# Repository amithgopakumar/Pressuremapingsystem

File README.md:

# ESP32 PCB designed for using FSR sensor to measure the pressure

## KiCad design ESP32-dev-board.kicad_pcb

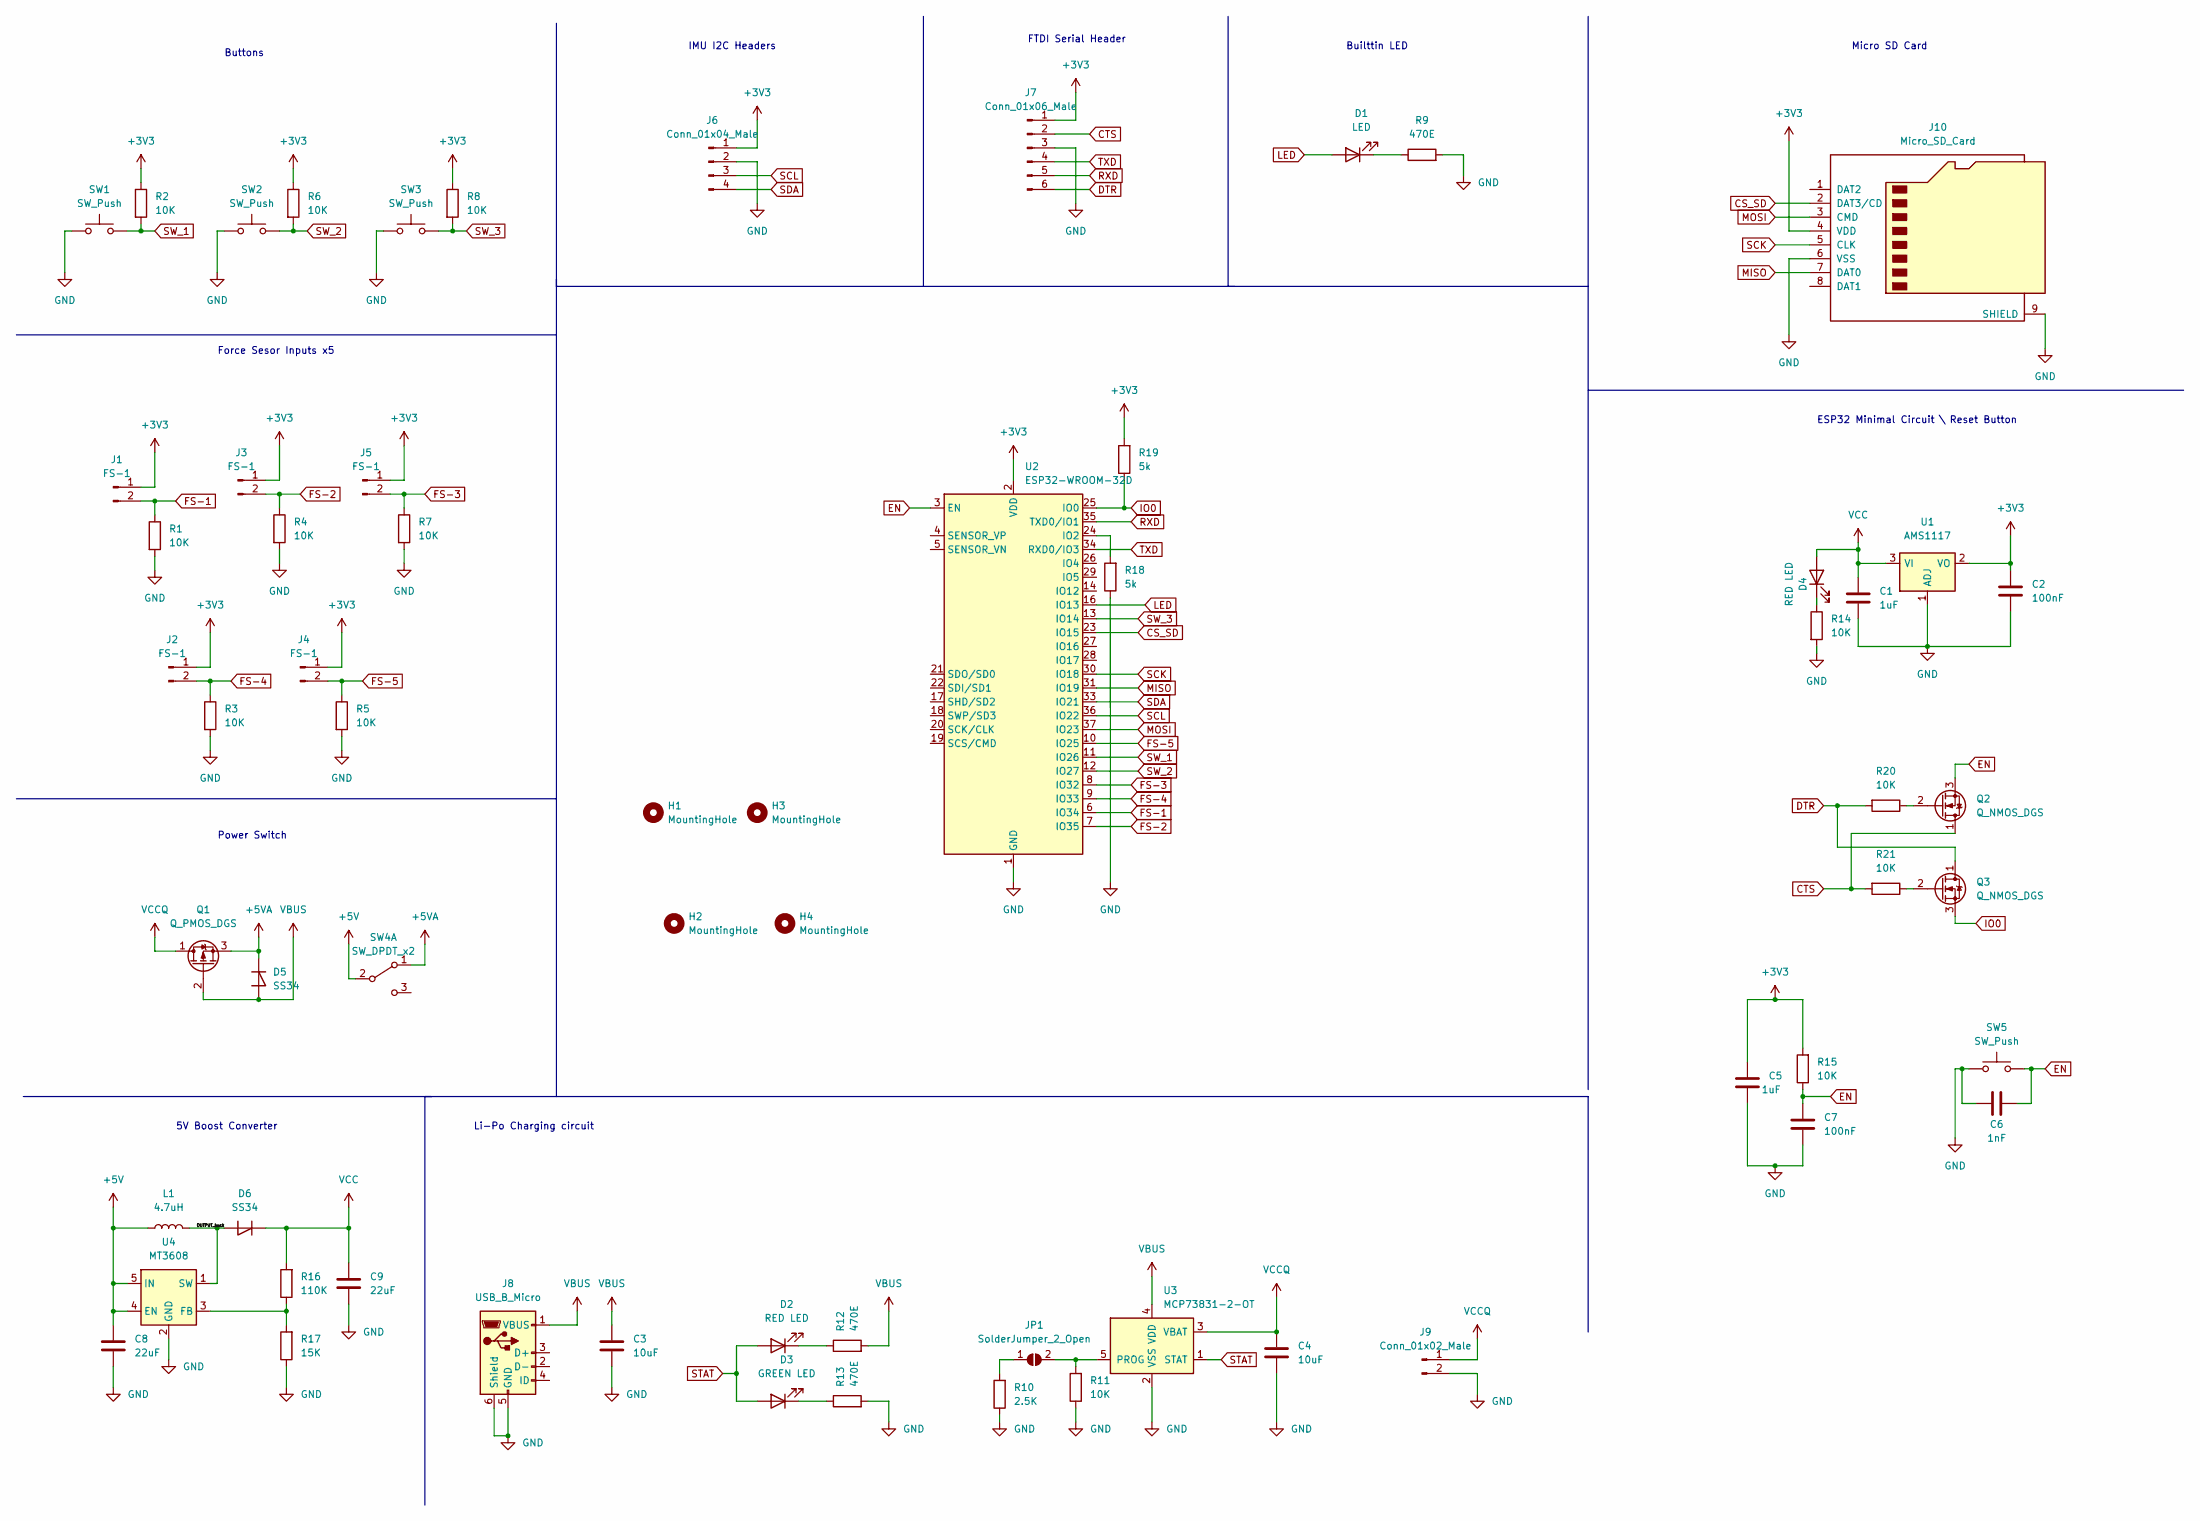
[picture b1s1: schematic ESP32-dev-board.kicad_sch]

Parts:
C1, C5: 1uF; C_1206_3216Metric_Pad1.33x1.80mm_HandSolder
C2, C7: 100nF; C_1206_3216Metric_Pad1.33x1.80mm_HandSolder
C3, C4: 10uF; C_1206_3216Metric_Pad1.33x1.80mm_HandSolder
C6: 1nF; C_1206_3216Metric_Pad1.33x1.80mm_HandSolder
C8, C9: 22uF; C_1206_3216Metric_Pad1.33x1.80mm_HandSolder
D1: LED; LED_1206_3216Metric_Pad1.42x1.75mm_HandSolder
D2, D4: RED LED; LED_1206_3216Metric_Pad1.42x1.75mm_HandSolder
D3: GREEN LED; LED_1206_3216Metric_Pad1.42x1.75mm_HandSolder
D5, D6: SS34; D_2512_6332Metric_Pad1.52x3.35mm_HandSolder
H1, H2, H3, H4: MountingHole; MountingHole_3.2mm_M3
J1, J2, J3, J4, J5: FS-1; JST_EH_S2B-EH_1x02_P2.50mm_Horizontal
J6: Conn_01x04_Male; JST_EH_B4B-EH-A_1x04_P2.50mm_Vertical
J7: Conn_01x06_Male; JST_EH_B6B-EH-A_1x06_P2.50mm_Vertical
J8: USB_B_Micro; MUP-U513 - 5 Pin Micro USB Female Connector
J9: Conn_01x02_Male; JST_EH_S2B-EH_1x02_P2.50mm_Horizontal
J10: Micro_SD_Card; GCT_MEM2075-00-140-01-A
JP1: SolderJumper_2_Open; SolderJumper-2_P1.3mm_Open_RoundedPad1.0x1.5mm
L1: 4.7uH; L_Taiyo-Yuden_NR-60xx_HandSoldering
Q1: Q_PMOS_DGS; SOT-23
Q2, Q3: Q_NMOS_DGS; SOT-23
R1, R2, R3, R4, R5, R6, R7, R8, R11, R14, R15, R20, R21: 10K; R_1206_3216Metric_Pad1.30x1.75mm_HandSolder
R9, R12, R13: 470E; R_1206_3216Metric_Pad1.30x1.75mm_HandSolder
R10: 2.5K; R_1206_3216Metric_Pad1.30x1.75mm_HandSolder
R16: 110K; R_1206_3216Metric_Pad1.30x1.75mm_HandSolder
R17: 15K; R_1206_3216Metric_Pad1.30x1.75mm_HandSolder
R18, R19: 5k; R_1206_3216Metric_Pad1.30x1.75mm_HandSolder
SW1, SW2, SW3, SW5: SW_Push; SW_Push_1P1T_NO_CK_KSC7xxJ
SW4: SW_DPDT_x2; SW_SPDT_PCM12
U1: AMS1117; SOT-223-3_TabPin2
U2: ESP32-WROOM-32D; ESP32-WROOM-32
U3: MCP73831-2-OT; SOT-23-5
U4: MT3608; SOT-23-6

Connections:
+3V3: C2.1, C5.1, J1.1, J2.1, J3.1, J4.1, J5.1, J6.1, J7.1, J10.4 (VDD), R2.1, R6.1, R8.1, R15.2, R19.2, U1.2 (VO), U2.2 (VDD)
+5V: C8.1, L1.1, SW4.2 (B), U4.4 (EN), U4.5 (IN)
+5VA: D5.1 (K), Q1.3 (S), SW4.1 (A)
/OUTPUT_buck: D6.2 (A), L1.2, U4.1 (SW)
CS_SD: J10.2 (DAT3/CD), U2.23 (IO15)
CTS: J7.2, Q2.1 (D), R21.2
DTR: J7.6, Q3.1 (D), R20.2
EN: C6.2, C7.1, Q2.3 (S), R15.1, SW5.2, U2.3 (EN)
FS-1: J1.2, R1.1, U2.6 (IO34)
FS-2: J3.2, R4.1, U2.7 (IO35)
FS-3: J5.2, R7.1, U2.8 (IO32)
FS-4: J2.2, R3.1, U2.9 (IO33)
FS-5: J4.2, R5.1, U2.10 (IO25)
GND: C1.2, C2.2, C3.2, C4.2, C5.2, C6.1, C7.2, C8.2, C9.2, J6.2, J7.3, J8.5 (GND), J8.6 (Shield), J9.2, J10.6 (VSS), J10.9 (SHIELD), R1.2, R3.2, R4.2, R5.2, R7.2, R9.2, R10.1, R11.1, R13.2, R14.2, R17.1, R18.1, SW1.1, SW2.1, SW3.1, SW5.1, U1.1 (ADJ), U2.1 (GND), U2.15 (GND), U2.38 (GND), U2.39 (GND), U3.2 (VSS), U4.2 (GND)
IO0: Q3.3 (S), R19.1, U2.25 (IO0)
LED: D1.2 (A), U2.16 (IO13)
MISO: J10.7 (DAT0), U2.31 (IO19)
MOSI: J10.3 (CMD), U2.37 (IO23)
unnamed: D1.1 (K), R9.1
unnamed: D2.1 (K), R12.1
unnamed: D3.1 (K), R13.1
unnamed: D4.1 (K), R14.1
unnamed: JP1.1 (A), R10.2
unnamed: JP1.2 (B), R11.2, U3.5 (PROG)
unnamed: Q2.2 (G), R20.1
unnamed: Q3.2 (G), R21.1
unnamed: R16.1, R17.2, U4.3 (FB)
unnamed: R18.2, U2.24 (IO2)
RXD: J7.5, U2.35 (TXD0/IO1)
SCK: J10.5 (CLK), U2.30 (IO18)
SCL: J6.3, U2.36 (IO22)
SDA: J6.4, U2.33 (IO21)
STAT: D2.2 (A), D3.2 (A), U3.1 (STAT)
SW_1: R2.2, SW1.2, U2.11 (IO26)
SW_2: R6.2, SW2.2, U2.12 (IO27)
SW_3: R8.2, SW3.2, U2.13 (IO14)
TXD: J7.4, U2.34 (RXD0/IO3)
VBUS: C3.1, D5.2 (A), J8.1 (VBUS), Q1.2 (G), R12.2, U3.4 (VDD)
VCC: C1.1, C9.1, D4.2 (A), D6.1 (K), R16.2, U1.3 (VI)
VCCQ: C4.1, J9.1, Q1.1 (D), U3.3 (VBAT)

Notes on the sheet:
ESP32 Minimal Circuit \ Reset Button
Force Sesor Inputs x5
FTDI Serial Header
Buttons
IMU I2C Headers
5V Boost Converter
Power Switch
Builttin LED
Li-Po Charging circuit
Micro SD Card

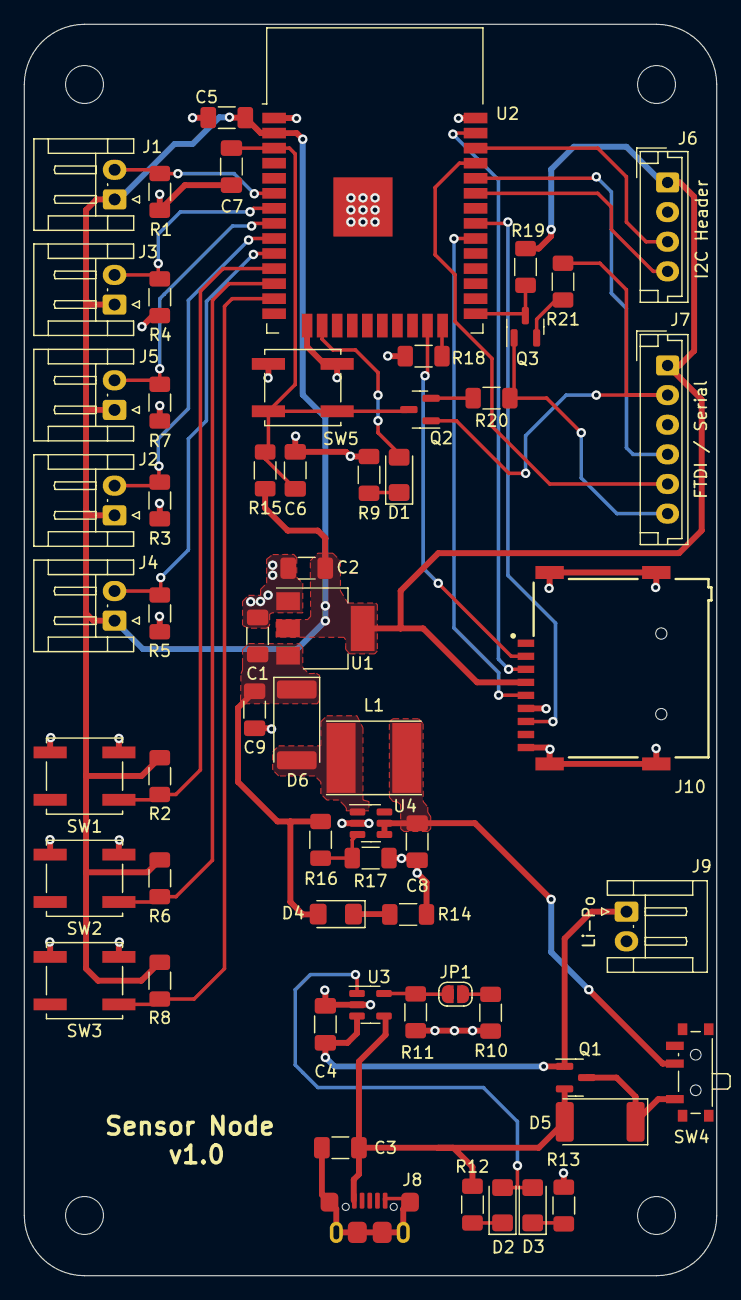
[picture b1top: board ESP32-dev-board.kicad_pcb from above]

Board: 2 copper layers, 58.4 x 105.6 mm, 64 parts (0 on the bottom side), 40 nets.

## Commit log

2024-06-26 Gerber update
